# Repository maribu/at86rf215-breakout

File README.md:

AT86RF215 Breakout Board
========================

This Repository contains an minimal AT86RF215 breakout board. The pin header
is compatible to the openlabs.co Raspberry Pi 802.15.4 radio. However, this
will not be a drop-in replacement as the software needs adjustment.

WARNING
=======

1. The PCB contains no shielding for the RF filter, which will result in lower
   sensitivity and higher noise in the transmitted signal compared to e.g. the
   AT86RF215-XPRO reference design.
2. It is highly recommended to not order PCBs based on this design as of now.
   While an earlier version seems to work flawlessly, this revision has not been
   tested yet.
3. There is absolutely no warranty.

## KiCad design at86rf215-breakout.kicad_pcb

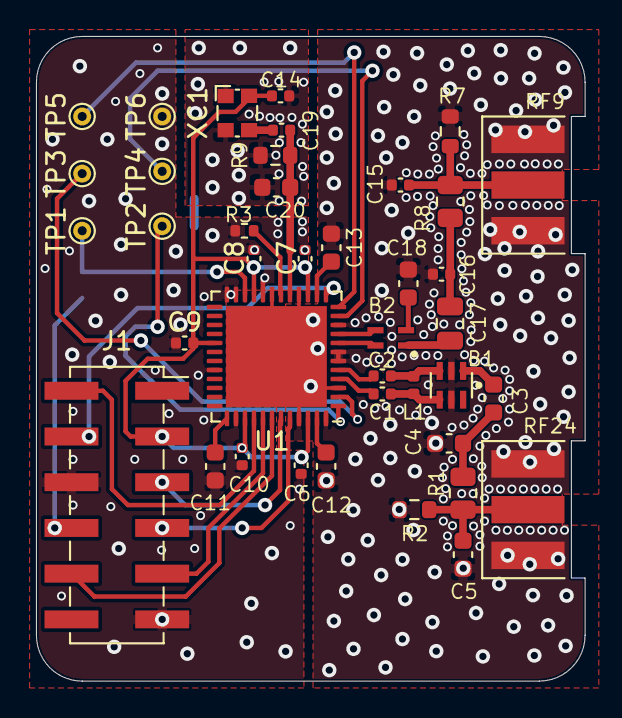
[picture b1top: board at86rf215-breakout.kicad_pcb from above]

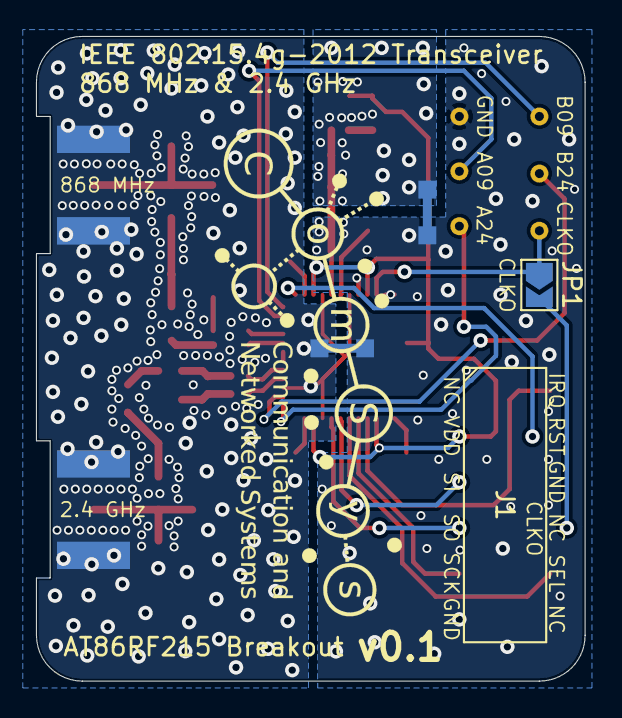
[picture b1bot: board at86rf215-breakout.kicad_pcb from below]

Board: 2 copper layers, 30.5 x 35.8 mm, 43 parts (3 on the bottom side), 35 nets.

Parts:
B1: Balun 2.4 GHz; 2450FB15A050
B2: Balun 868 MHz; DLW21SN900SQ2L
C1, C2: 1.8 pF; C_0402_1005Metric
C3: 0.8 pF; C_0603_1608Metric
C4, C5: 1.2 pF; C_0603_1608Metric
C6, C7, C8, C9, C10, C14: 100 nF; C_0402_1005Metric
C11, C12, C13: 1 µF; C_0603_1608Metric
C15, C16: 2.2 pF; C_0402_1005Metric
C17: 15 pF; C_0805_2012Metric
C18: 8.2 pF; C_0603_1608Metric
C19: 1 nF; C_0402_1005Metric
C20: 10 pF; C_0603_1608Metric
J1: RPi Header; PinSocket_2x06_P2.54mm_Vertical_SMD
JP1: solder jumper; SolderJumper-2_P1.3mm_Open_TrianglePad1.0x1.5mm
L1: 5.6 nH; L_0402_1005Metric
R1, R8: 0 Ω; R_0805_2012Metric
R2, R7, R9: 10 kΩ; R_0603_1608Metric
R3: 100 kΩ; R_0402_1005Metric
R4, R5: 0 Ω; R0
RF9, RF24: Antenna; Connector-SMA
TP1: CLKO; TestPoint_THTPad_D1.0mm_Drill0.5mm
TP2: FEA24; TestPoint_THTPad_D1.0mm_Drill0.5mm
TP3: FEB24; TestPoint_THTPad_D1.0mm_Drill0.5mm
TP4: FEA09; TestPoint_THTPad_D1.0mm_Drill0.5mm
TP5: FEB09; TestPoint_THTPad_D1.0mm_Drill0.5mm
TP6: GND; TestPoint_THTPad_D1.0mm_Drill0.5mm
U1: AT86RF215-ZU; QFN-48-1EP_7x7mm_P0.5mm_EP5.6x5.6mm
XC1: 26 MHz TCXO; IQD_LFTCXO078374REEL

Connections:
/ANT09: C15.1, R7.1, R8.2, RF9.1
/ANT09': C16.1, C17.2, R8.1
/ANT09'': B2.1, C17.1
/ANT24: C5.1, R1.2, R2.1, RF24.1
/ANT24': C3.1, C4.1, R1.1
/ANT24'': B1.1, C3.2
/AVDD0: C13.2, U1.14
/AVDD1: C12.2, U1.47
/Balun_GND: B2.2, C18.1
/CLKO: JP1.1, TP1.1, U1.22
/CLKO': J1.8, JP1.2
/DVDD: C11.2, U1.37
/FEA09: TP4.1, U1.11
/FEA24: TP2.1, U1.1
/FEB09: TP5.1, U1.12
/FEB24: TP3.1, U1.2
/IRQ: J1.2, U1.40
/MISO: J1.7, U1.44
/MOSI: J1.5, U1.43
/RFN09: B2.3, U1.9
/RFN24: C2.2, U1.5
/RFN24': B1.3, C2.1, L1.2
/RFP09: B2.4, U1.8
/RFP24: C1.2, U1.4
/RFP24': B1.4, C1.1, L1.1
/RST: J1.4, U1.13
/SCLK: J1.9, U1.41
/SEL: J1.10, U1.42
/TCXO: C19.1, C20.1, R9.1, U1.17
/TCXO': C19.2, XC1.3
GND: C6.1, C7.1, C8.1, C9.1, C10.1, C11.1, J1.6, J1.11, R3.1, R4.2, R5.2, TP6.1, U1.20, U1.23, U1.24, U1.32, U1.38
GND2: C14.2, C20.2, R4.1, R9.2, XC1.1, XC1.2
GNDA: B1.2, B1.5, C4.2, C5.2, C12.1, C13.1, C15.2, C16.2, C18.2, R2.2, R5.1, R7.2, RF9.2, RF24.2, U1.3, U1.6, U1.7, U1.10, U1.16, U1.19, U1.45, U1.48, U1.49
unnamed: R3.2, U1.18
VDD: C6.2, C7.2, C8.2, C9.2, C10.2, C14.1, J1.3, U1.15, U1.21, U1.29, U1.39, U1.46, XC1.4

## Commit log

2020-11-23 Update to v0.1
    - Use SMD instead for thru-hole pin header for lower assembly cost
    - Place pin header on top side, so that only one side needs SMD assembly
    - Move pin header to allow placement on MIoT-Lab Testbed Nodes
2020-11-25 Add custom panelization script
    The KiKit CLI cannot create a grid with boards rotated differently, so I created
    a custom script using KiKit to create the panels. This places two rows of the
    board with the SMA connector facing outward, so that they can be soldered on
    by the fab without breaking the boards of out the panel.
2020-11-26 Use same baluns as AT86RF215-XPRO
2020-11-30 Added test points
2020-12-01 Use different TCXO
2020-12-02 Change used TCXO
2020-12-18 Fixed footprint of TCXO
    Datasheet is in bottom view, not top view :-/
2021-01-21 PCB: Untick "Keep upright" on labels
    This makes sure that the rotated PCBs on the panel have identically oriented
    silkscreen labels in both rows :-)
